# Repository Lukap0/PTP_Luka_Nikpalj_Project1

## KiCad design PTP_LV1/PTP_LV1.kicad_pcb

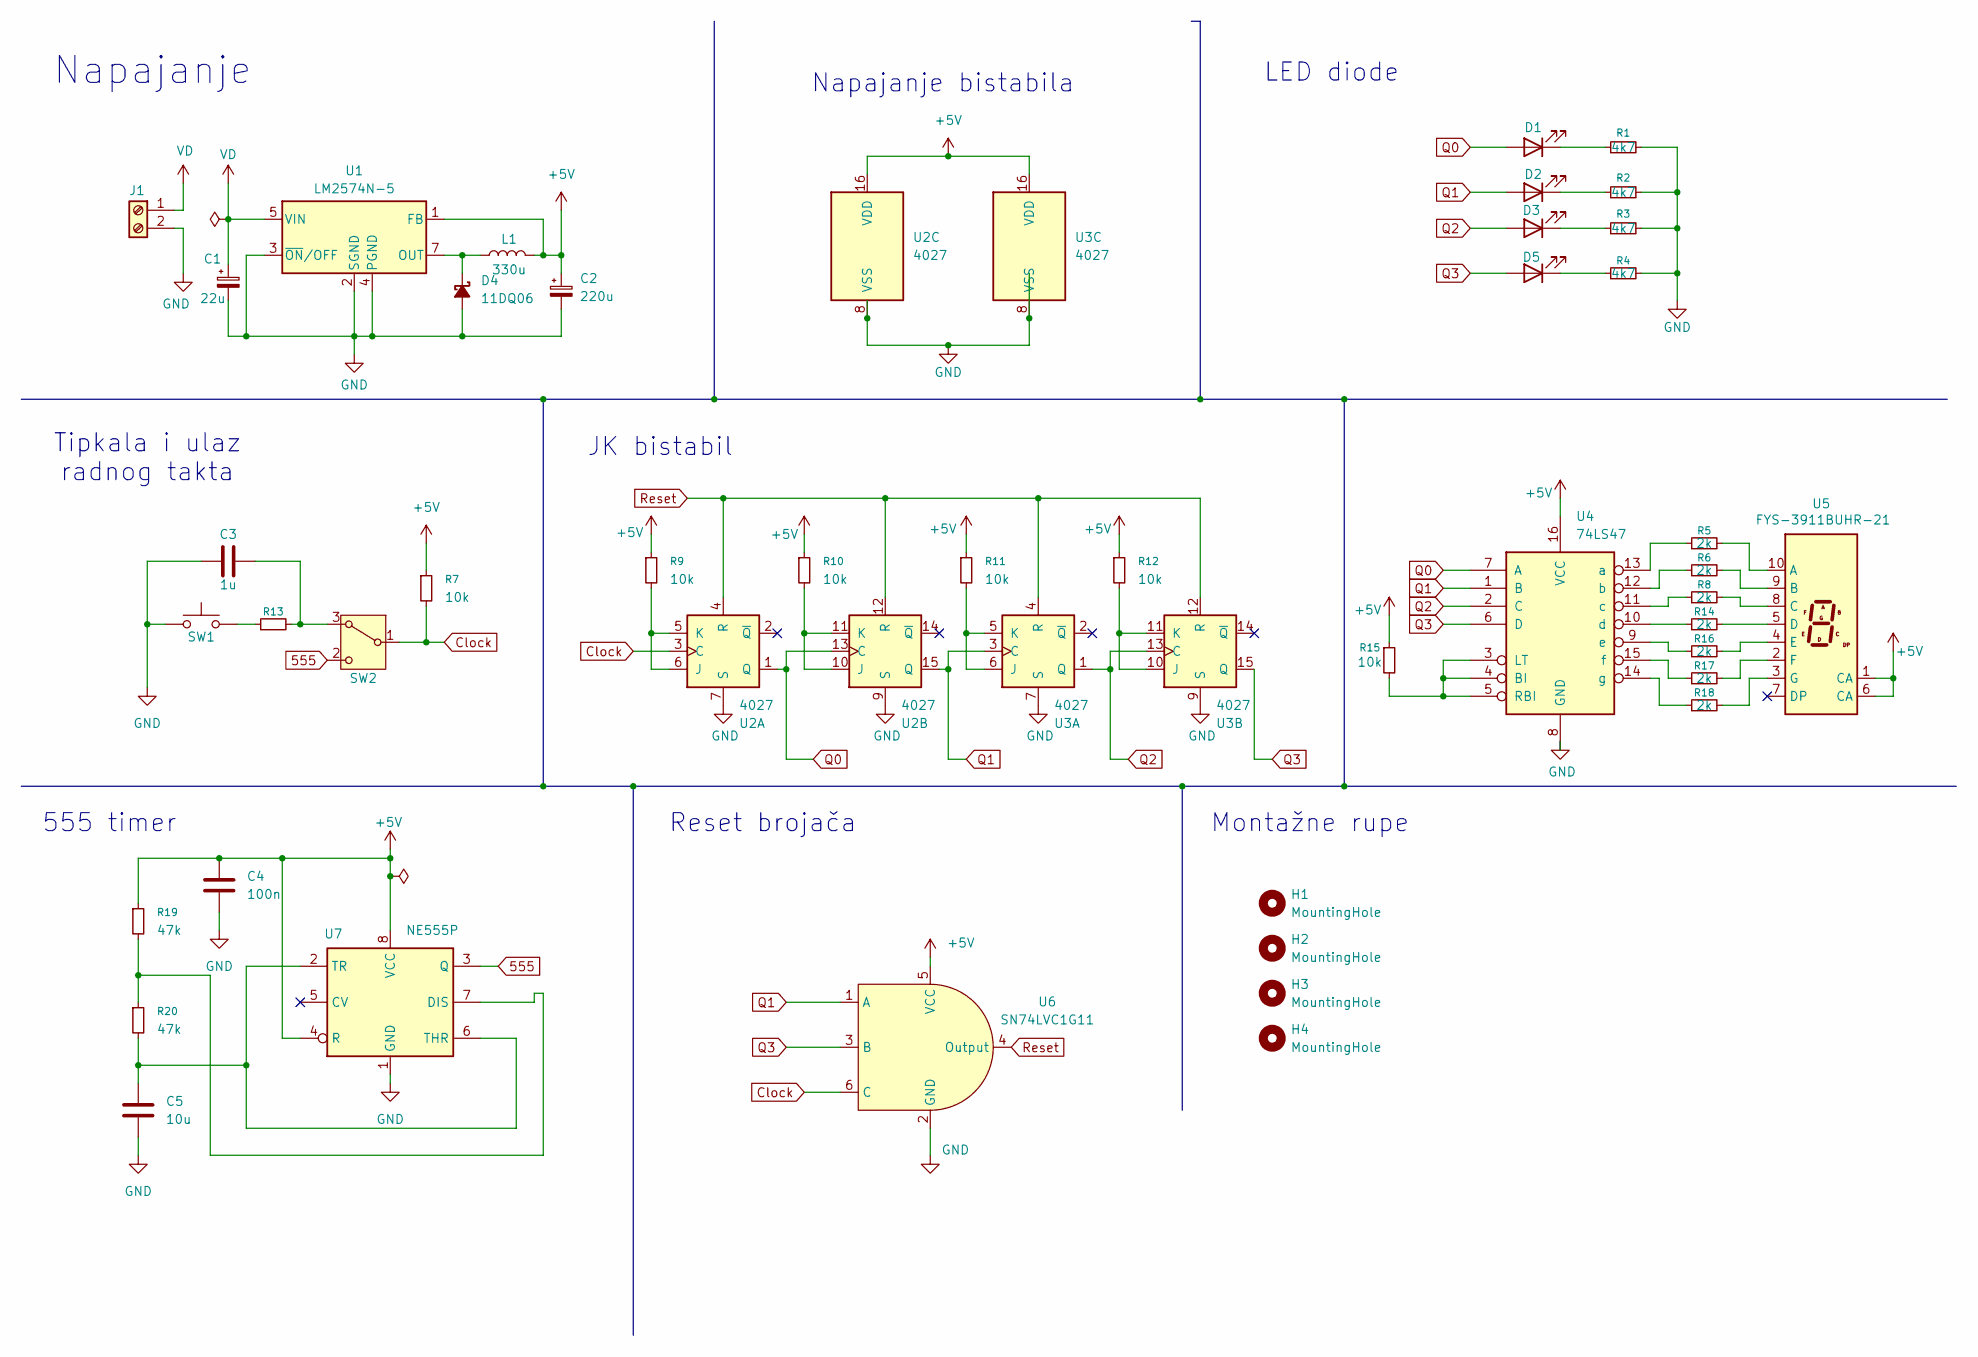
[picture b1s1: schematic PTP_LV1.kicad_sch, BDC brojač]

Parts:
C1: 22u; CP_Radial_D5.0mm_P2.00mm; Manufacturer part number EWH1EM220D11OT
C2: 220u; CP_Radial_D5.0mm_P2.00mm; Manufacturer part number RD1A227M05011BB
C3: 1u; C_1206_3216Metric_Pad1.33x1.80mm_HandSolder; Manufacturer part number CL31B105KBHNNNE
C4: 100n; C_1206_3216Metric_Pad1.33x1.80mm_HandSolder; Manufacturer part number CL31B104KBCNNNC
C5: 10u; C_1206_3216Metric_Pad1.33x1.80mm_HandSolder; Manufacturer part number CL31A106KBHNNNE
D1, D2, D3, D5: LED_D5.0mm
D4: 11DQ06; D_DO-41_SOD81_P12.70mm_Horizontal; Manufacturer part number 11DQ06TA
H1, H2, H3, H4: MountingHole; MountingHole_5.5mm
J1: TerminalBlock_MetzConnect_Type011_RT05502HBLC_1x02_P5.00mm_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; Manufacturer part Number DG301-5.0-02P-12-00A(H)
L1: 330u; L_Radial_D7.2mm_P3.00mm_Murata_1700; Manufacturer Part Number COIL0608-0.33
R1, R2, R3, R4: 4k7; R_Axial_DIN0207_L6.3mm_D2.5mm_P10.16mm_Horizontal
R5, R16, R17: 2k; R_1206_3216Metric_Pad1.30x1.75mm_HandSolder; Manufacturer part Number 1206S4F2001T5E
R6, R13, R18: 2k; R_1206_3216Metric_Pad1.30x1.75mm_HandSolder; Manufacturer part number 1206S4F2001T5E
R7, R9, R10, R11, R12, R15: 10k; R_1206_3216Metric_Pad1.30x1.75mm_HandSolder
R8, R14: 2k; R_1206_3216Metric_Pad1.30x1.75mm_HandSolder; Manufacturer Part Number 1206S4F2001T5E
R19, R20: 47k; R_1206_3216Metric_Pad1.30x1.75mm_HandSolder; Manufacturer part Number 1206S4J0473T5E
SW1: SW_PUSH_6mm_H4.3mm; Manufacturer part number TACT-64N-F
SW2: SW_Slide_SPDT_Straight_CK_OS102011MS2Q; Manufacturer Part Number OS102011MS2QN1C
U1: LM2574N-5; DIP-8_W7.62mm_Socket_LongPads; Manufacturer part number LM2574N-5G
U2, U3: 4027; DIP-16_W7.62mm_Socket_LongPads; Manufacturer part number CD4027BMS
U4: 74LS47; DIP-16_W7.62mm_Socket_LongPads; Manufacturer Part Number SN74LS47N
U5: FYS-3911BUHR-21; HDSP-7401; Manufacturer Part Number FYS-3911BUHR-21
U6: SN74LVC1G11; SOT-23-6; Manufacturer Part Numbe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 SN74LVC1G11DBVR
U7: NE555P; DIP-8_W7.62mm; Manufacturer Part Number NE555P

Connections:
555: SW2.2 (C), U7.3 (Q)
+5V: C2.1, C4.1, L1.2, R7.1, R9.1, R10.1, R11.1, R12.1, R15.1, R19.1, U1.1 (FB), U2.16 (VDD), U3.16 (VDD), U4.16 (VCC), U5.1 (CA), U5.6 (CA), U6.5 (VCC), U7.4 (R), U7.8 (VCC)
Clock: R7.2, SW2.1 (B), U2.3 (C), U6.6 (C)
GND: C1.2, C2.2, C3.1, C4.2, C5.2, D4.2 (A), J1.2, R1.2, R2.2, R3.2, R4.2, SW1.1, U1.2 (SGND), U1.3 (~ON/OFF), U1.4 (PGND), U2.7 (S), U2.8 (VSS), U2.9 (S), U3.7 (S), U3.8 (VSS), U3.9 (S), U4.8 (GND), U6.2 (GND), U7.1 (GND)
unnamed: D1.1 (K), R1.1
unnamed: D2.1 (K), R2.1
unnamed: D3.1 (K), R3.1
unnamed: D4.1 (K), L1.1, U1.7 (OUT)
unnamed: D5.1 (K), R4.1
unnamed: R13.1, SW1.2
unnamed: C3.2, R13.2, SW2.3 (A)
unnamed: R9.2, U2.5 (K), U2.6 (J)
unnamed: R10.2, U2.10 (J), U2.11 (K)
unnamed: R11.2, U3.5 (K), U3.6 (J)
unnamed: R12.2, U3.10 (J), U3.11 (K)
unnamed: R15.2, U4.3 (LT), U4.4 (BI), U4.5 (RBI)
unnamed: R5.1, U4.13 (a)
unnamed: R6.1, U4.12 (b)
unnamed: R8.1, U4.11 (c)
unnamed: R14.1, U4.10 (d)
unnamed: R16.1, U4.9 (e)
unnamed: R17.1, U4.15 (f)
unnamed: R18.1, U4.14 (g)
unnamed: R5.2, U5.10 (A)
unnamed: R6.2, U5.9 (B)
unnamed: R8.2, U5.8 (C)
unnamed: R14.2, U5.5 (D)
unnamed: R16.2, U5.4 (E)
unnamed: R17.2, U5.2 (F)
unnamed: R18.2, U5.3 (G)
unnamed: R19.2, R20.1, U7.7 (DIS)
unnamed: C5.1, R20.2, U7.2 (TR), U7.6 (THR)
Q0: D1.2 (A), U2.1 (Q), U2.13 (C), U4.7 (A)
Q1: D2.2 (A), U2.15 (Q), U3.3 (C), U4.1 (B), U6.1 (A)
Q2: D3.2 (A), U3.1 (Q), U3.13 (C), U4.2 (C)
Q3: D5.2 (A), U3.15 (Q), U4.6 (D), U6.3 (B)
Reset: U2.4 (R), U2.12 (R), U3.4 (R), U3.12 (R), U6.4 (Output)
VD: C1.1, J1.1, U1.5 (VIN)

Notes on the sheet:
Reset brojača
Napajanje bistabila
Napajanje
555 timer
JK bistabil
LED diode
Montažne rupe
Tipkala i ulaz radnog takta

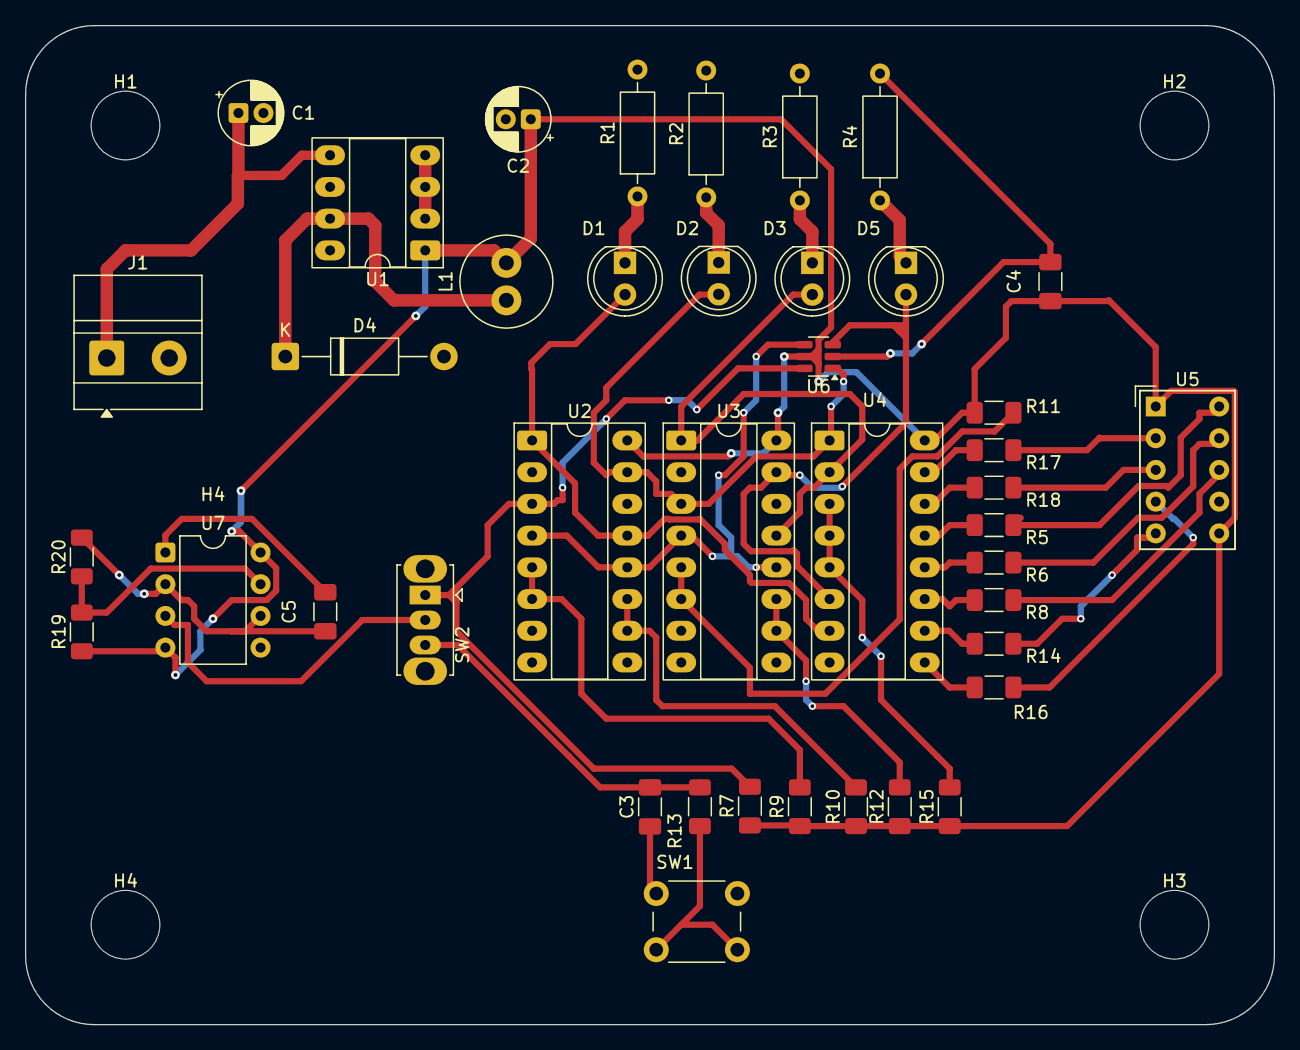
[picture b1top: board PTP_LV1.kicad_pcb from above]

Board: 2 copper layers, 100.0 x 80.0 mm, 45 parts (0 on the bottom side), 38 nets.

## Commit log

2025-10-21 ispunjena sastavnica
2025-10-28 LV2 Riješen
2025-11-04 LV3
    LV3 Dovršen
2025-11-11 LV4
    Zavrsili schemu i dodali neke footprinte (ostatak dodati doma)
2025-11-25 Dovrsia footprintove eli
    E to
2025-11-25 PTP LV5
    PCB editor slagali plocicu ka nesto
2025-12-03 PTP LV 5
    Napravaljeno ozicenje ali ne do kraja napravit doma mozda
2025-12-03 twe
    rtzert
2025-12-16 Nikpalj LV7
    sbe gotovo sad na seminar najjace
